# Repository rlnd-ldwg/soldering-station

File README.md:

# soldering-station
### based on Weller soldering tip

improved fork from ArduinoHannover/Maiskolben  

features:  
* optional referenzvoltage for A/D conversion based on LM4040
* optional PWM controlled TFT brightness
* using ATmega328p as mcu
* rotary encoder to set temperature
* prototyping area for own development
* voltage converter for I2C interface

for more information see the original README under README-MAISKOLBEN.md (german)

Beim Drehenkoder müssen A und S1 getauscht werden!

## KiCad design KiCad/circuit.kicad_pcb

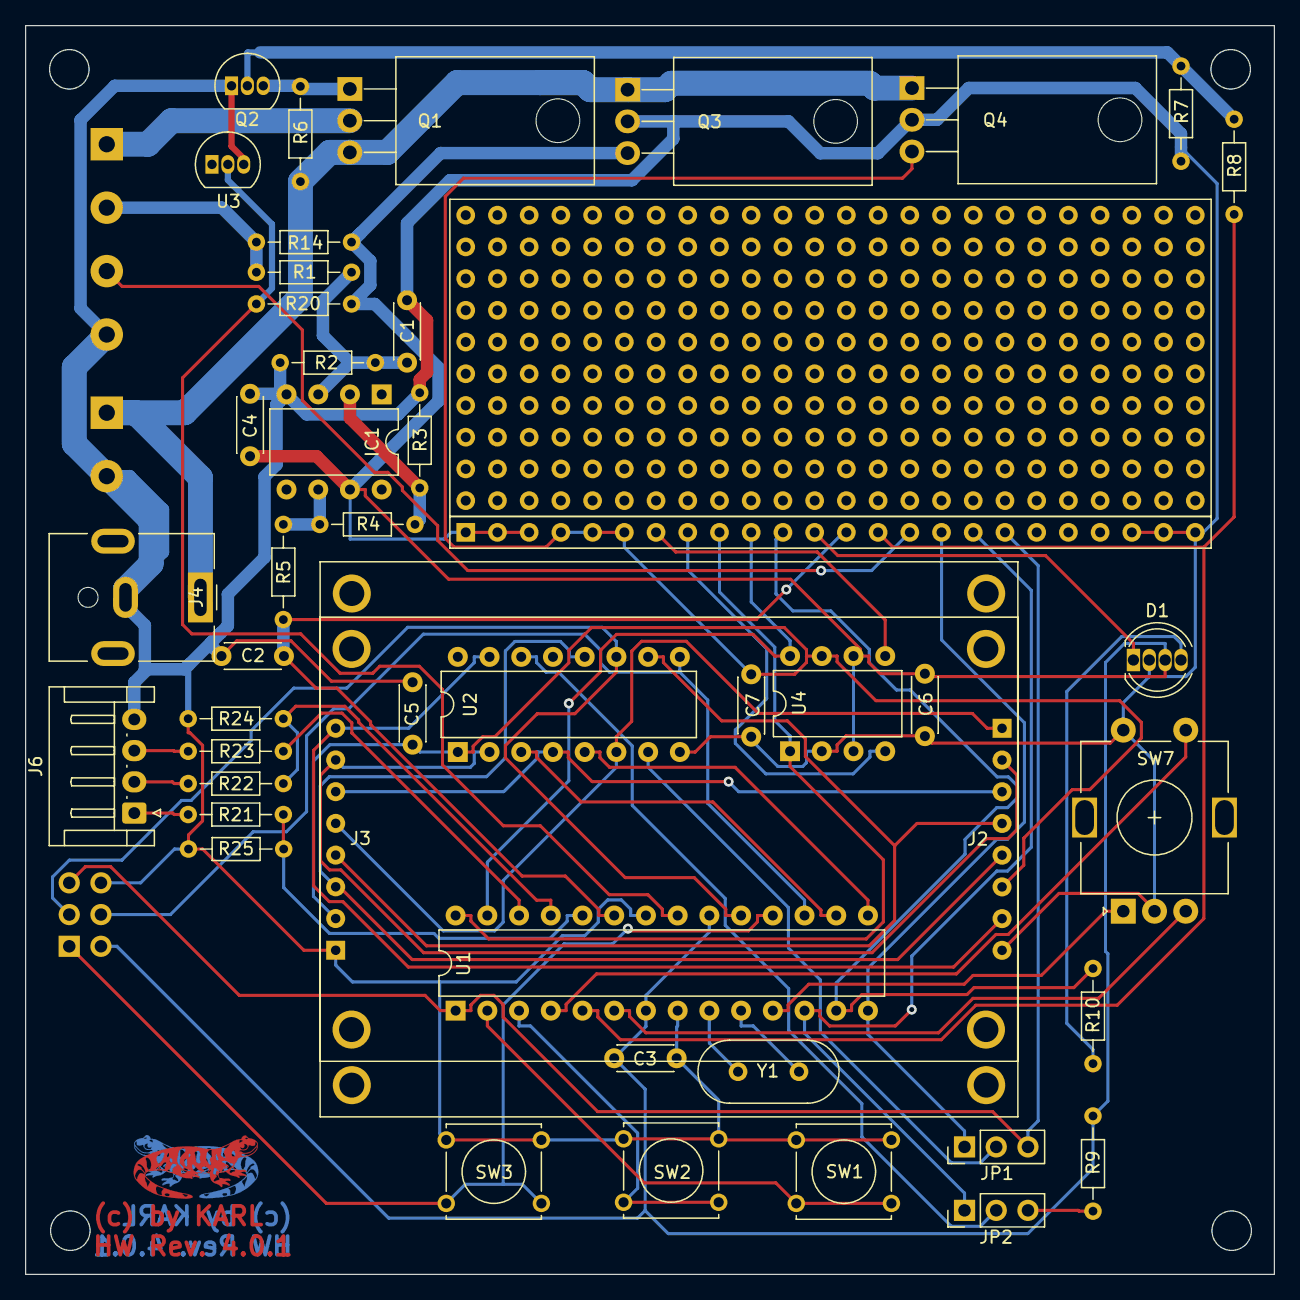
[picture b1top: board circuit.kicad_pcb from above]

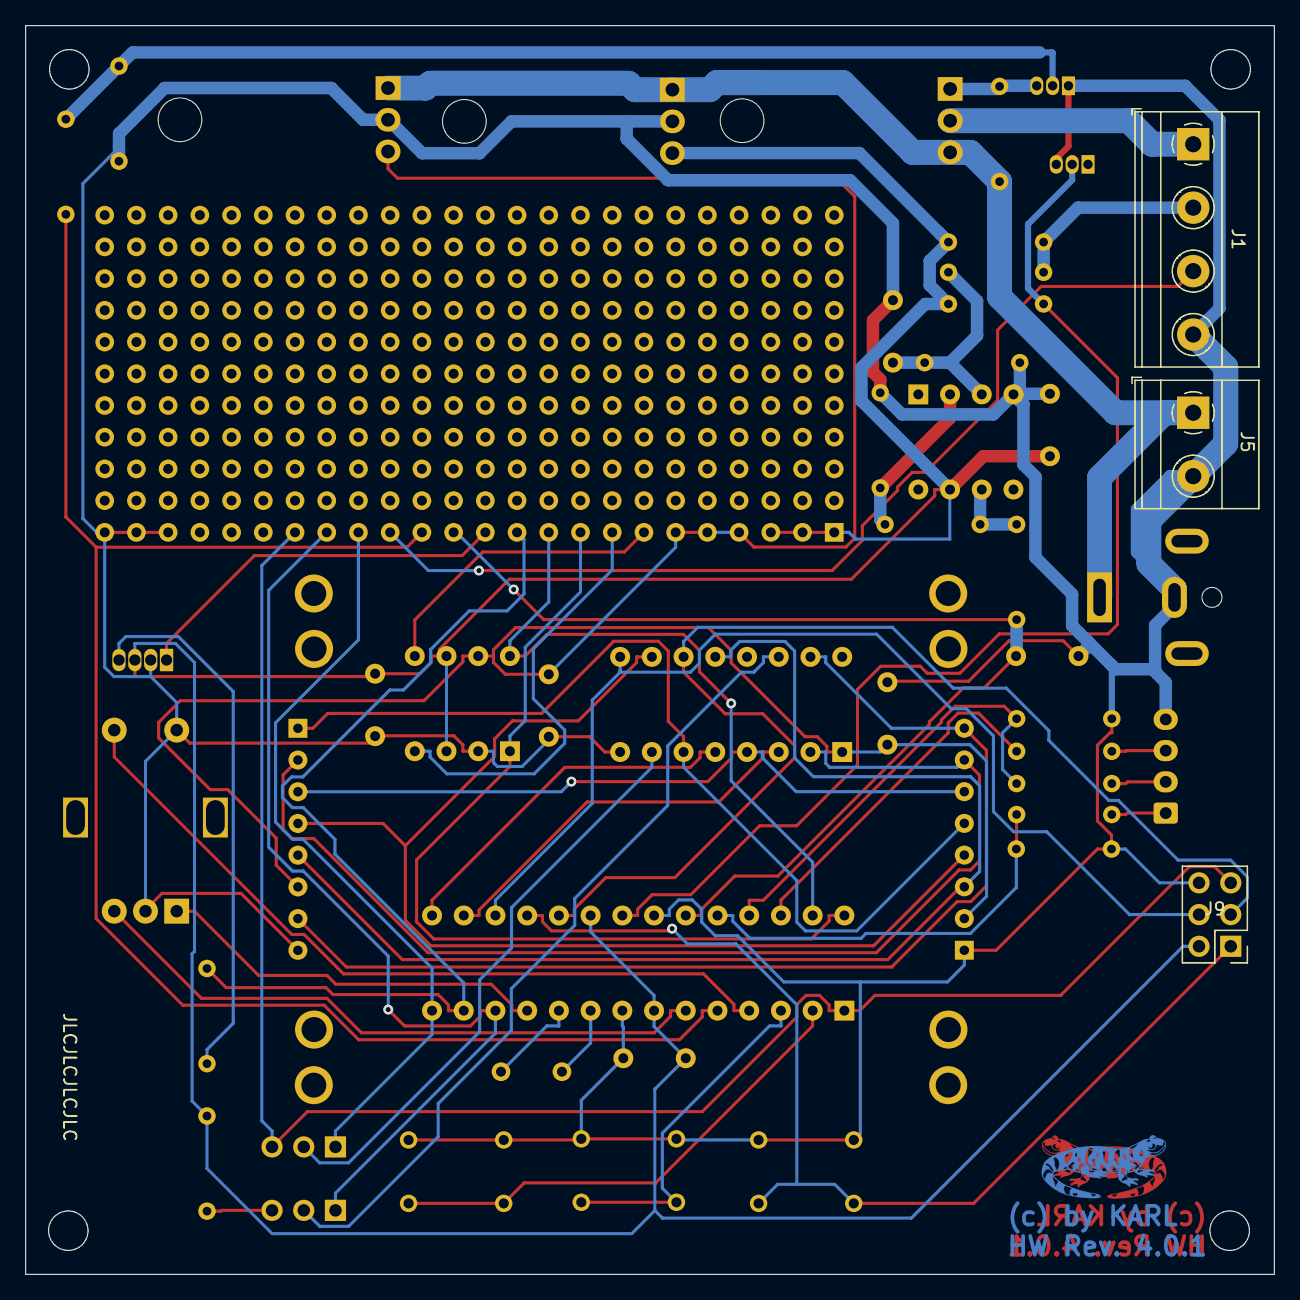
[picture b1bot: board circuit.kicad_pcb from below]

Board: 2 copper layers, 100.0 x 100.0 mm, 52 parts (4 on the bottom side), 52 nets.

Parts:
10x24: Proto10x24
C1: 10nF; C_Disc_D4.3mm_W1.9mm_P5.00mm
C2: C; C_Disc_D4.3mm_W1.9mm_P5.00mm
C3, C4, C5, C7: 100nF; C_Disc_D4.3mm_W1.9mm_P5.00mm
C6: 100nf; C_Disc_D4.3mm_W1.9mm_P5.00mm
D1: NeoPixel_THT; LED_D5.0mm-4_RGB
IC1: OP703PA; DIP-8_W7.62mm
J1: Soldering iron; TerminalBlock_Phoenix_MKDS-1,5-4-5.08_1x04_P5.08mm_Horizont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
J2: TFT AK; TFT-1.8-AK
J3: TFT RL; TFT-1.8-RGB
J4: 12V; BarrelJack_CUI_PJ-063AH_Horizontal
J5: Power 12V; TerminalBlock_Phoenix_MKDS-1,5-2-5.08_1x02_P5.08mm_Horizont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
J6: LiPo-Bal; JST_EH_S4B-EH_1x04_P2.50mm_Horizontal
J9: ISP; PinHeader_2x03_P2.54mm_Vertical
JP1: TFT Reset; PinHeader_1x03_P2.54mm_Vertical
JP2: BL Control; PinHeader_1x03_P2.54mm_Vertical
Logo1, Logo1#2: LOGO; Logo
Prototype1: Conn_01x24; Proto1x24
Q1: IRF5305; TO-220-3_Horizontal_TabDown
Q2: 2N7000; TO-92_Inline
Q3: LM7805; TO-220-3_Horizontal_TabDown
Q4: LM117T 3.3; TO-220-3_Horizontal_TabDown
R1, R5: 5,6kΩ; R_Axial_DIN0204_L3.6mm_D1.6mm_P7.62mm_Horizontal
R2: 100kΩ; R_Axial_DIN0204_L3.6mm_D1.6mm_P7.62mm_Horizontal
R3: 100Ω; R_Axial_DIN0204_L3.6mm_D1.6mm_P7.62mm_Horizontal
R4: 68kΩ; R_Axial_DIN0204_L3.6mm_D1.6mm_P7.62mm_Horizontal
R6, R7, R9: 10kΩ; R_Axial_DIN0204_L3.6mm_D1.6mm_P7.62mm_Horizontal
R8: 1kΩ; R_Axial_DIN0204_L3.6mm_D1.6mm_P7.62mm_Horizontal
R10: 220Ω/0Ω; R_Axial_DIN0204_L3.6mm_D1.6mm_P7.62mm_Horizontal
R14: 10MΩ; R_Axial_DIN0204_L3.6mm_D1.6mm_P7.62mm_Horizontal
R20: 560Ω; R_Axial_DIN0204_L3.6mm_D1.6mm_P7.62mm_Horizontal
R21: 2MΩ; R_Axial_DIN0204_L3.6mm_D1.6mm_P7.62mm_Horizontal
R22, R23, R24, R25: 1MΩ; R_Axial_DIN0204_L3.6mm_D1.6mm_P7.62mm_Horizontal
SW1: T1; SW_Tactile_Straight_KSL0Axx1LFTR
SW2: T2; SW_Tactile_Straight_KSL0Axx1LFTR
SW3: T3; SW_Tactile_Straight_KSL0Axx1LFTR
SW7: Menu; RotaryEncoder_Alps_EC11E-Switch_Vertical_H20mm
U1: ATmega328-PU; DIP-28_W7.62mm
U2: 4050; DIP-16_W7.62mm
U3: LM4040LP-4.1; TO-92_Inline
U4: TXS0102DCT; DIP-8_W7.62mm
Y1: 16MHz; Crystal_HC49-U_Vertical

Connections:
+3V3: C5.2, C7.1, J2.6, J3.2, Prototype1.4, Prototype1.5, Prototype1.6, Q4.3, U2.1, U4.7
+5V: C3.1, C4.1, C6.2, D1.3, IC1.7, J9.2, Prototype1.1, Prototype1.2, Prototype1.3, Q3.3, R9.1, R14.1, R20.2, U1.7, U1.20, U4.3, U4.6
+12V: J4.1, J5.1, Q1.3, Q3.1, Q4.1, R6.1
AREF: R20.1, U1.21, U3.2
BL: JP2.1, Prototype1.17, U1.12
CS: U1.16, U2.3
DC: U1.15, U2.5
Down: SW7.A, U1.11
GNDD: C1.2, C2.1, C3.2, C4.2, C5.1, C6.1, C7.2, D1.2, IC1.4, J1.4, J2.8, J3.1, J4.2, J5.2, J6.4, J9.6, Prototype1.22, Prototype1.23, Prototype1.24, Q2.1, Q3.2, Q4.2, R2.2, R3.1, R7.2, R24.2, R25.2, SW1.1, SW2.1, SW3.1, SW7.C, SW7.S2, U1.8, U1.22, U2.8, U3.3, U4.2
LiPo1: R23.1, U1.26
LiPo2: R22.1, R24.1, U1.25
LiPo3: R21.1, R25.1, U1.24
MISO: J9.1, SW3.2, U1.18
MOSI: J9.4, U1.17, U2.9
unnamed: C1.1, IC1.3, R1.1, R2.1
unnamed: D1.1, Prototype1.12
unnamed: D1.4, R10.2
unnamed: IC1.2, R3.2, R4.1
unnamed: IC1.6, R4.2, R5.2
unnamed: J1.1, Q1.2
unnamed: J1.2, R1.2, R14.2
unnamed: J2.1, J3.5, U2.6
unnamed: J2.2, J3.7, U2.2
unnamed: J2.3, J3.6, U2.4
unnamed: J2.4, J3.4, U2.10
unnamed: J2.5, J3.3, U2.12
unnamed: J2.7, J3.8, U2.15
unnamed: J6.1, R21.2
unnamed: J6.2, R22.2
unnamed: J6.3, R23.2
unnamed: JP1.2, U2.7
unnamed: JP2.2, U2.14
unnamed: JP2.3, R9.2
unnamed: Prototype1.11, R10.1, U1.13
unnamed: Q1.1, Q2.3, R6.2
unnamed: Q2.2, R7.1, R8.2
unnamed: U1.9, Y1.2
unnamed: U1.10, Y1.1
Pow: SW7.S1, U1.4
Res: J9.5, JP1.3, Prototype1.18, U1.1
SCK: J9.3, U1.19, U2.11
SCL: Prototype1.9, U1.28, U4.1
SCL5V: Prototype1.8, U4.4
SDA: Prototype1.10, U1.27, U4.8
SDA5V: Prototype1.7, U4.5
Sensor: C2.2, Prototype1.13, R5.1, U1.23
T1: SW1.2, U1.2
T2: SW2.2, U1.3
TFT-RST: JP1.1, Prototype1.16, U1.14
Tip: Prototype1.14, R8.1, U1.5
Tip2: J1.3, Prototype1.15
Up: SW7.B, U1.6

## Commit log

2020-02-19 v0.0.1
2020-02-19 v0.0.2
2020-02-21 v0.0.3
2020-02-22 v0.0.4
2020-02-22 v0.0.5
2020-02-22 v0.0.6 (USE_TFT_REST)
2020-02-24 add #SERIAL
2020-02-24 v0.0.7
    OLED Display improvement
2020-02-24 change SERIAL
2020-02-24 comment out battery code (USE_LIPO)
2020-02-25 v1.0
2020-02-25 v0.0.7
2020-02-25 v0.0.8
2020-02-26 v1.0.1
    add external AREF
    change step to +/- 5
2020-02-26 v0.0.9 pcb v1.0.2 changed USE_TFT_RESET in main.cpp
2020-02-28 v0.0.10
2020-02-28 v0.0.11
2020-02-29 v1.0.2
2020-02-29 v0.0.12
2020-02-29 v0.0.13
2020-03-01 v1.0.1 / HW Rev. 4.0.1
2020-03-01 v1.0.1
2020-03-03 v1.0.0
2020-03-05 Create dummy
2020-03-05 Lötspitzehalter V1
2020-03-05 Lötspitzenhalter als STL
2020-03-11 v1.0.2 split configuration -> config.h
2020-03-11 v1.0.3
2020-03-16 v1.0.5 minor changes in schematic and pcb
2020-03-29 switch button 1 & 3 / direction rotary encoder
2021-03-23 Version 1.0
